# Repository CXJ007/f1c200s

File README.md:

# f1c200s
做这个板子最初目的就是白嫖正点原子的教程，如果买板子按照我以前学习经历大多都是学习下外设那些的然后板子就吃灰了  
这个板子大部分都已经调通了（除了声音因为忘记买芯片后面过年又鸽了）  
还有值得注意的就是usbid 也就是pe2一不注意给占用了，板子上缺少按键学习的时候不太方便  

我是第一次画4层板，还是有很多不足的地方，用来学习应该没问题  
大致流程就是在社区帮助下移植好linux就可以白嫖了注意设备树添加是不一样的  
kicad6.0 ubuntu18 linux5.7.1  
最后附上社区地址https://whycan.com/

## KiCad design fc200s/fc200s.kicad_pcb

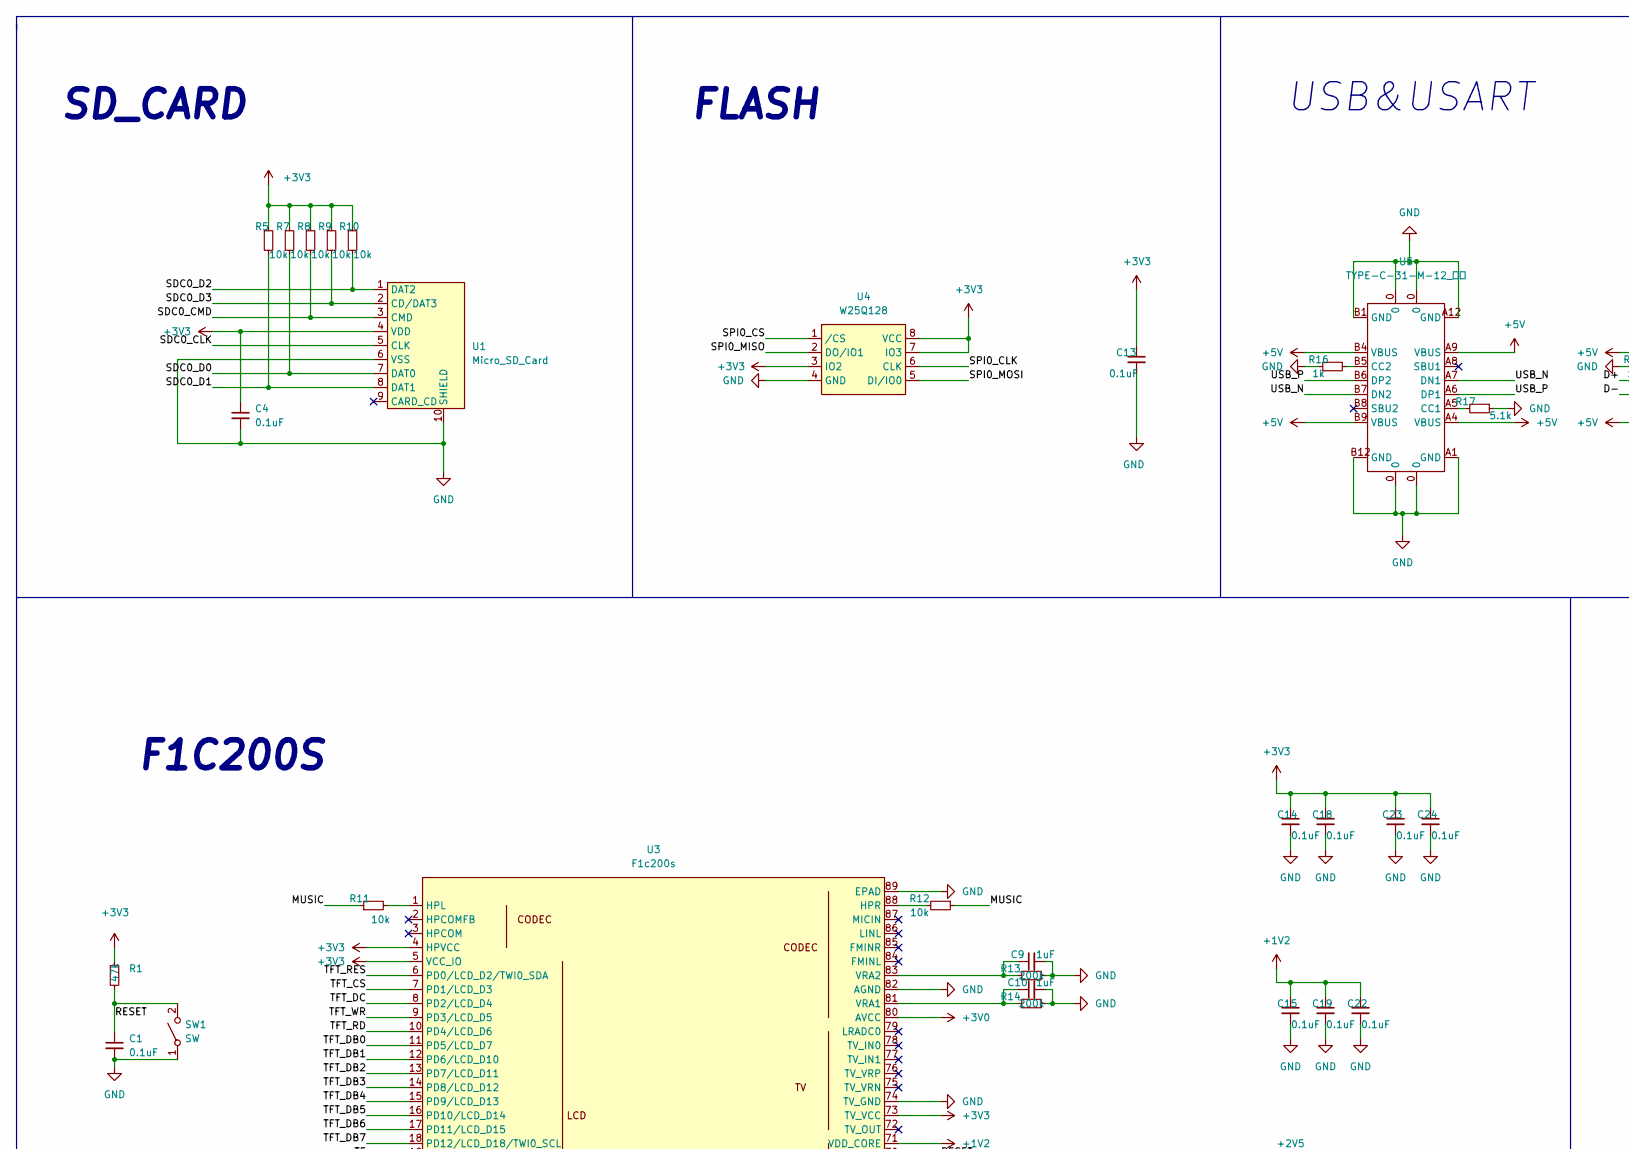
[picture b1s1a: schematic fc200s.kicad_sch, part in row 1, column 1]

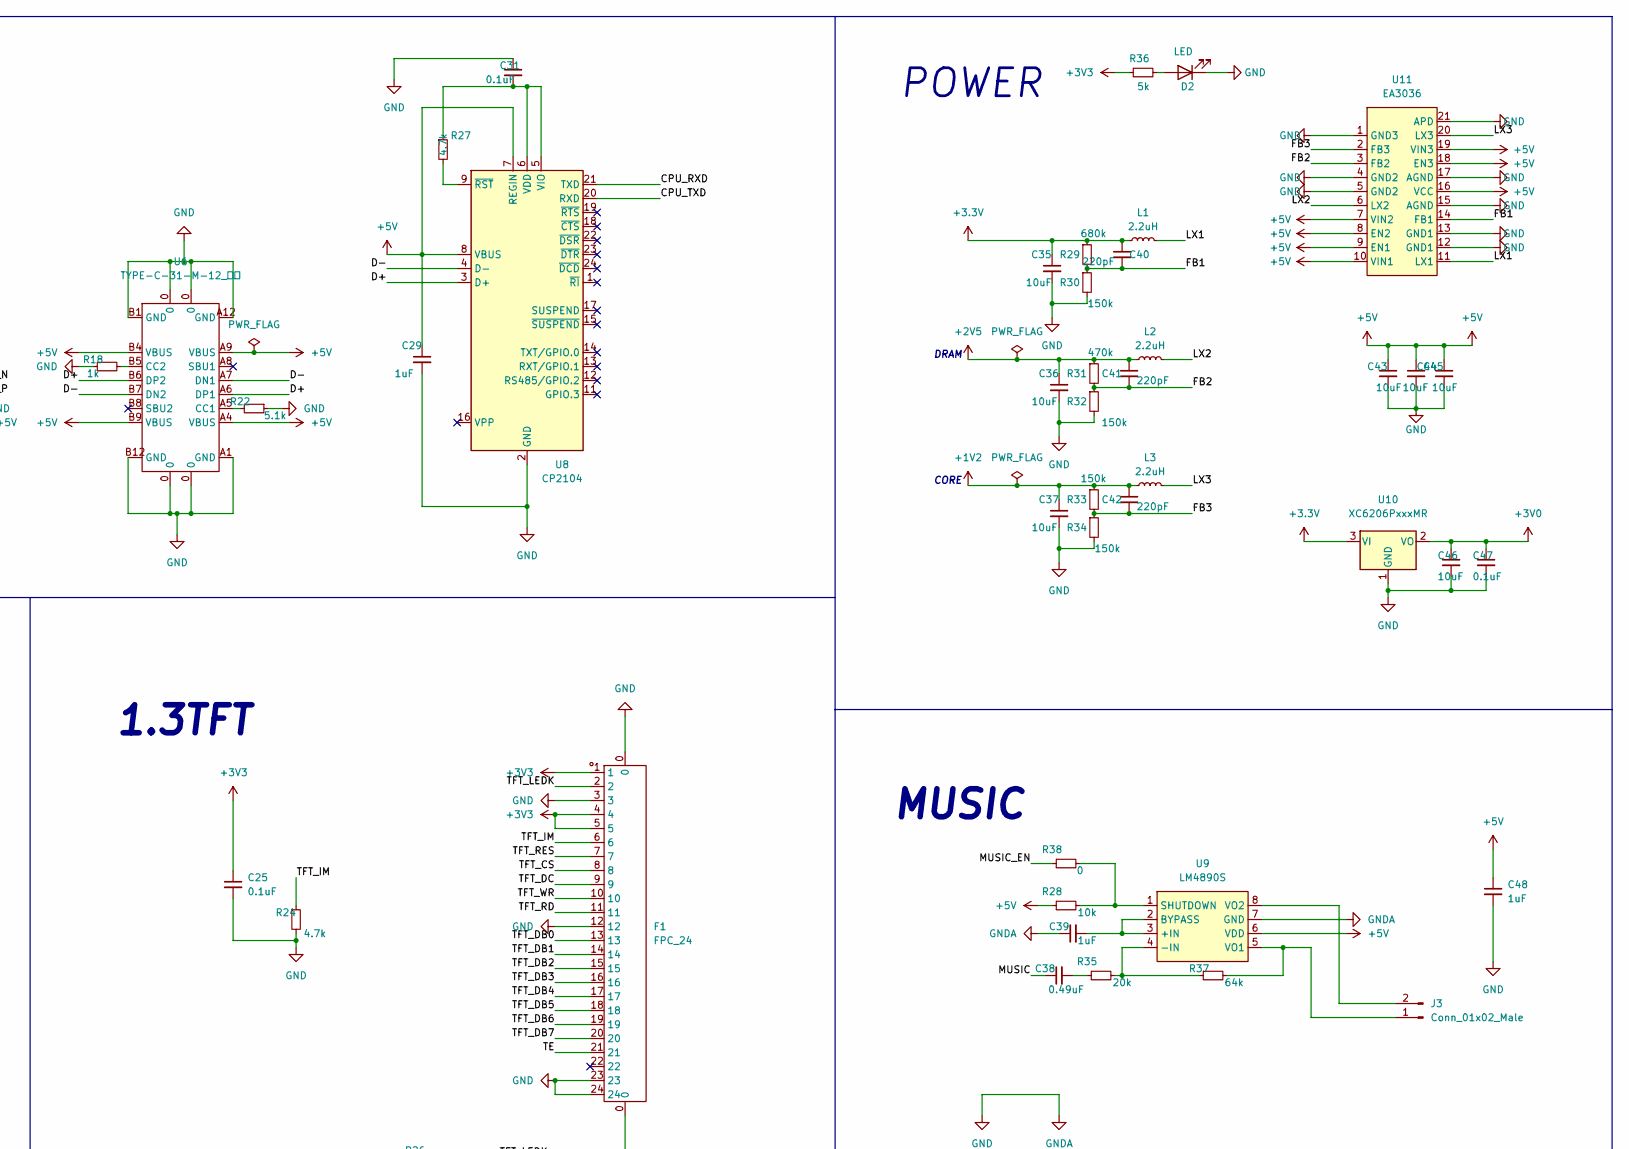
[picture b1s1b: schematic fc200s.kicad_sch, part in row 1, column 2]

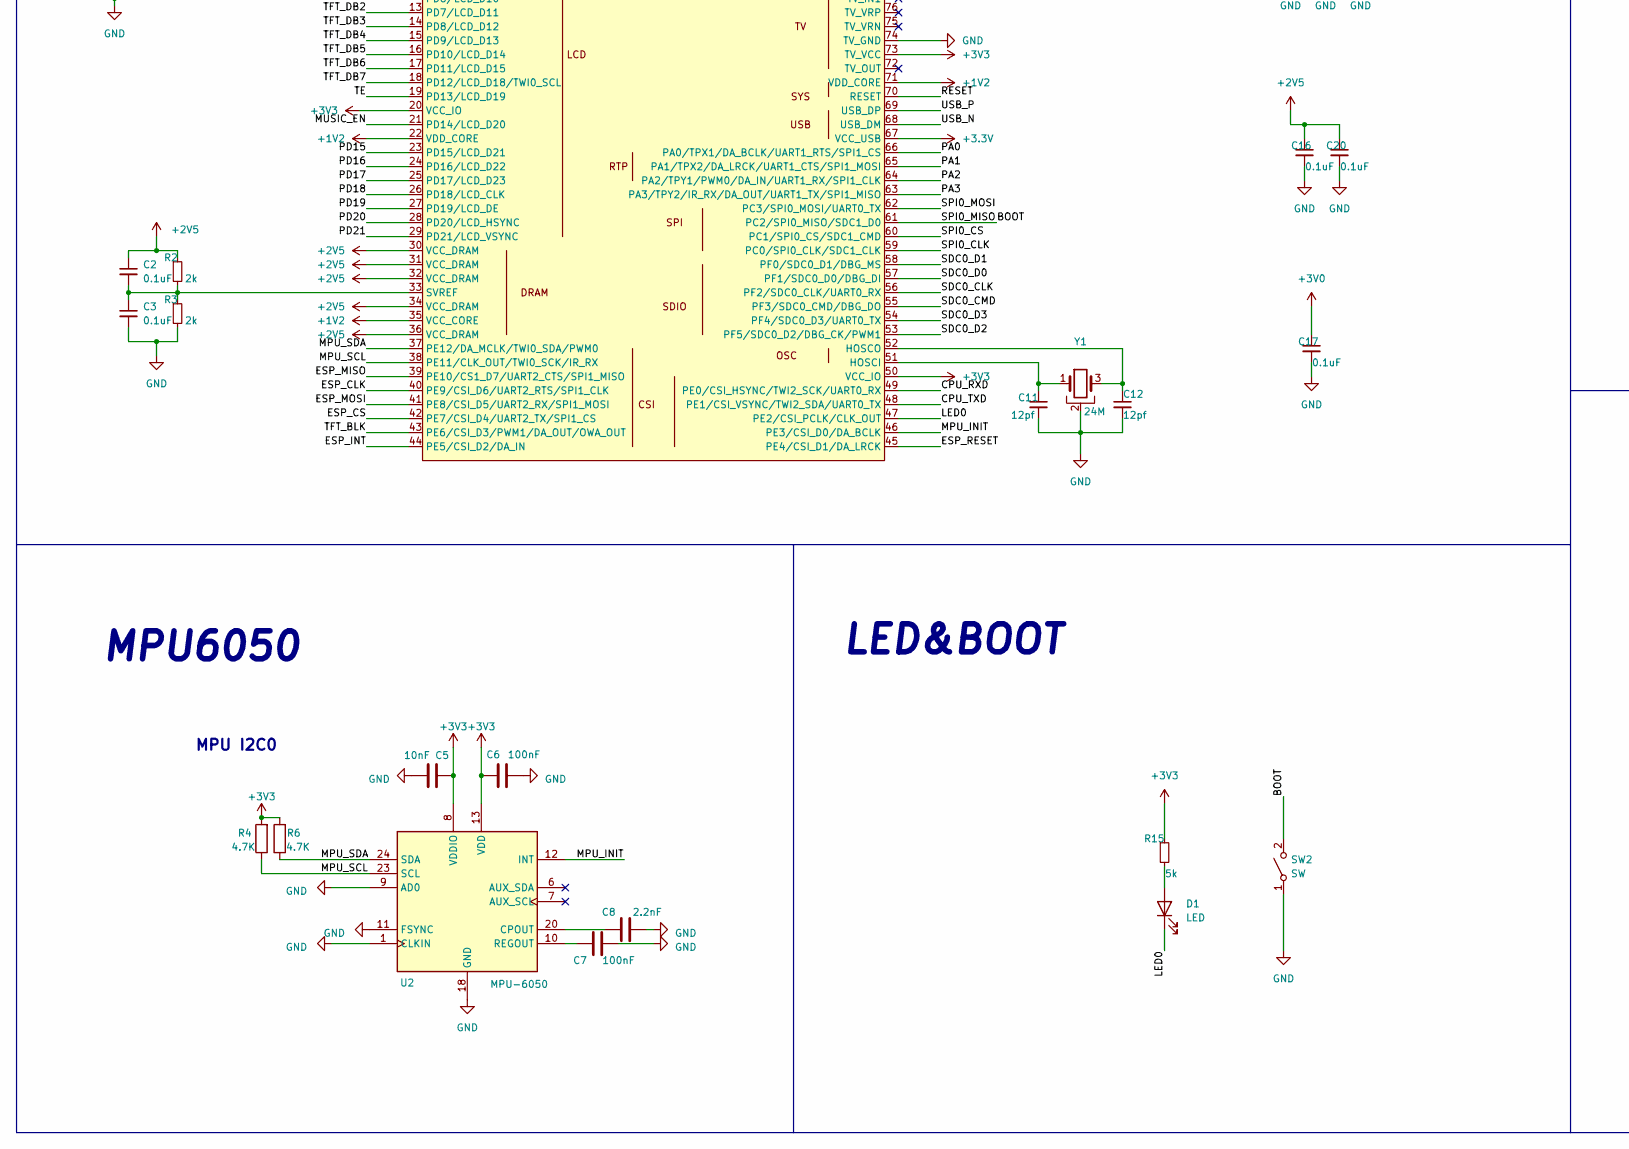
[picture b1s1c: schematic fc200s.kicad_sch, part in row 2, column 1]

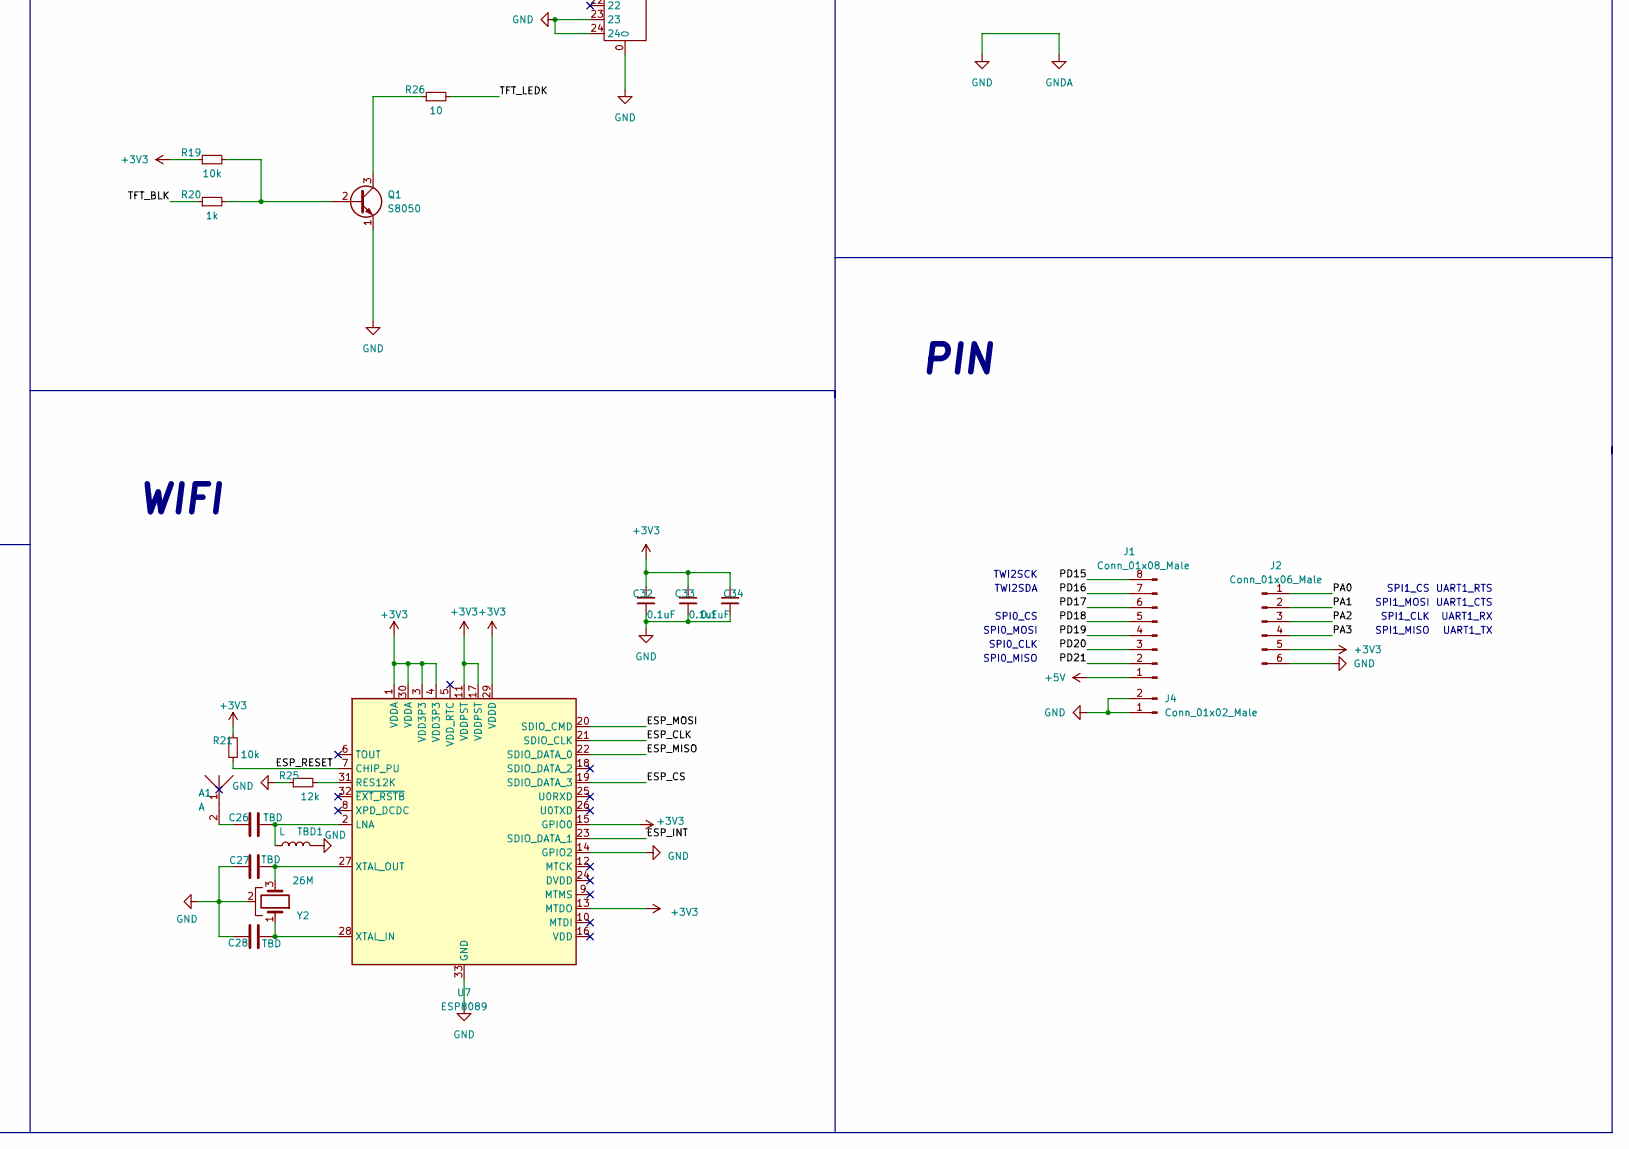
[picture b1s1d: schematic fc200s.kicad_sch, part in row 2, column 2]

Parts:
A1: A; AN9520-245
C1, C2, C3, C4, C13, C14, C15, C16, C17, C18, C19, C20, C22, C23, C24, C25, C31, C32, C33, C34, C47: 0.1uF; C_0805_2012Metric
C5: 10nF; C_0805_2012Metric
C6, C7: 100nF; C_0805_2012Metric
C8: 2.2nF; C_0805_2012Metric
C9, C10, C29, C39, C48: 1uF; C_0805_2012Metric
C11, C12: 12pf; C_0805_2012Metric
C26, C27, C28: TBD; C_0805_2012Metric
C35, C36, C37, C43, C44, C45, C46: 10uF; C_0805_2012Metric
C38: 0.49uF; C_0805_2012Metric
C40, C41, C42: 220pF; C_0805_2012Metric
D1, D2: LED; LED_0805_2012Metric
F1: FPC_24; FPC_24_0.5
J1: Conn_01x08_Male; 8p_2.54
J2: Conn_01x06_Male; 6p_2.54
J3, J4: Conn_01x02_Male; 2p_2.54
L1, L2, L3: 2.2uH; L_0805_2012Metric
Q1: S8050; S8050_SOT_23
R1: 47k; R_0805_2012Metric
R2, R3: 2k; R_0805_2012Metric
R4, R6: 4.7K; R_0805_2012Metric
R5, R7, R8, R9, R10, R11, R12, R19, R21, R28: 10k; R_0805_2012Metric
R13, R14: 200k; R_0805_2012Metric
R15, R36: 5k; R_0805_2012Metric
R16, R18, R20: 1k; R_0805_2012Metric
R17, R22: 5.1k; R_0805_2012Metric
R24, R27: 4.7k; R_0805_2012Metric
R25: 12k; R_0805_2012Metric
R26: 10; R_0805_2012Metric
R29: 680k; R_0805_2012Metric
R30, R32, R33, R34: 150k; R_0805_2012Metric
R31: 470k; R_0805_2012Metric
R35: 20k; R_0805_2012Metric
R37: 64k; R_0805_2012Metric
R38: 0; R_0805_2012Metric
SW1, SW2: SW
TBD1: L; L_0805_2012Metric
U1: Micro_SD_Card; Micro_SD
U2: MPU-6050; InvenSense_QFN-24_4x4mm_P0.5mm
U3: F1c200s; QFN-88_EP_10x10_Pitch0.4mm
U4: W25Q128
U5, U6: TYPE-C-31-M-12_母座; typec 12
U7: ESP8089; QFN-32-1EP_5x5mm_P0.5mm_EP3.1x3.1mm_ThermalVias
U8: CP2104; QFN-24-1EP_4x4mm_P0.5mm_EP2.6x2.6mm
U9: LM4890S; LM4890S_MSOP_8
U10: XC6206PxxxMR; SOT-23
U11: EA3036; QFN-20-1EP_3x3mm_P0.4mm_EP1.65x1.65mm
Y1: 24M; X322512MSB4S
Y2: 26M; X322512MSB4S

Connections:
+1V2: C15.1, C19.1, C22.1, C37.1, C42.1, L3.1, R33.1, U3.22 (VDD_CORE), U3.35 (VCC_CORE), U3.71 (VDD_CORE)
+2V5: C2.1, C16.1, C20.1, C36.1, C41.1, L2.1, R2.1, R31.1, U3.30 (VCC_DRAM), U3.31 (VCC_DRAM), U3.32 (VCC_DRAM), U3.34 (VCC_DRAM), U3.36 (VCC_DRAM)
+3V0: C17.1, C46.1, C47.1, U3.80 (AVCC), U10.2 (VO)
+5V: C29.1, C43.1, C44.1, C45.1, C48.1, J1.1, R28.1, U5.A4 (VBUS), U5.A9 (VBUS), U5.B4 (VBUS), U5.B9 (VBUS), U6.A4 (VBUS), U6.A9 (VBUS), U6.B4 (VBUS), U6.B9 (VBUS), U8.7 (REGIN), U8.8 (VBUS), U9.6 (VDD), U11.7 (VIN2), U11.8 (EN2), U11.9 (EN1), U11.10 (VIN1), U11.16 (VCC), U11.18 (EN3), U11.19 (VIN3)
/BOOT: SW2.2 (B), U3.61 (PC2/SPI0_MISO/SDC1_D0), U4.2 (DO/IO1)
/CPU_RXD: U3.49 (PE0/CSI_HSYNC/TWI2_SCK/UART0_RX), U8.21 (TXD)
/CPU_TXD: U3.48 (PE1/CSI_VSYNC/TWI2_SDA/UART0_TX), U8.20 (RXD)
/D+: U6.A6 (DP1), U6.B6 (DP2), U8.3 (D+)
/D-: U6.A7 (DN1), U6.B7 (DN2), U8.4 (D-)
/ESP_CLK: U3.40 (PE9/CSI_D6/UART2_RTS/SPI1_CLK), U7.21 (SDIO_CLK)
/ESP_CS: U3.42 (PE7/CSI_D4/UART2_TX/SPI1_CS), U7.19 (SDIO_DATA_3)
/ESP_INT: U3.44 (PE5/CSI_D2/DA_IN), U7.23 (SDIO_DATA_1)
/ESP_MISO: U3.39 (PE10/CS1_D7/UART2_CTS/SPI1_MISO), U7.22 (SDIO_DATA_0)
/ESP_MOSI: U3.41 (PE8/CSI_D5/UART2_RX/SPI1_MOSI), U7.20 (SDIO_CMD)
/ESP_RESET: R21.2, U3.45 (PE4/CSI_D1/DA_LRCK), U7.7 (CHIP_PU)
/FB1: C40.2, R29.2, R30.1, U11.14 (FB1)
/FB2: C41.2, R31.2, R32.1, U11.3 (FB2)
/FB3: C42.2, R33.2, R34.1, U11.2 (FB3)
/LED0: D1.1 (K), U3.47 (PE2/CSI_PCLK/CLK_OUT)
/LX1: L1.2, U11.11 (LX1)
/LX2: L2.2, U11.6 (LX2)
/LX3: L3.2, U11.20 (LX3)
/MPU_INIT: U2.12 (INT), U3.46 (PE3/CSI_D0/DA_BCLK)
/MPU_SCL: R4.1, U2.23 (SCL), U3.38 (PE11/CLK_OUT/TWI0_SCK/IR_RX)
/MPU_SDA: R6.1, U2.24 (SDA), U3.37 (PE12/DA_MCLK/TWI0_SDA/PWM0)
/MUSIC: C38.1, R11.1, R12.1
/MUSIC_EN: R38.1, U3.21 (PD14/LCD_D20)
/PA0: J2.1, U3.66 (PA0/TPX1/DA_BCLK/UART1_RTS/SPI1_CS)
/PA1: J2.2, U3.65 (PA1/TPX2/DA_LRCK/UART1_CTS/SPI1_MOSI)
/PA2: J2.3, U3.64 (PA2/TPY1/PWM0/DA_IN/UART1_RX/SPI1_CLK)
/PA3: J2.4, U3.63 (PA3/TPY2/IR_RX/DA_OUT/UART1_TX/SPI1_MISO)
/PD15: J1.8, U3.23 (PD15/LCD_D21)
/PD16: J1.7, U3.24 (PD16/LCD_D22)
/PD17: J1.6, U3.25 (PD17/LCD_D23)
/PD18: J1.5, U3.26 (PD18/LCD_CLK)
/PD19: J1.4, U3.27 (PD19/LCD_DE)
/PD20: J1.3, U3.28 (PD20/LCD_HSYNC)
/PD21: J1.2, U3.29 (PD21/LCD_VSYNC)
/RESET: C1.1, R1.2, SW1.2 (B), U3.70 (RESET)
/SDC0_CLK: U1.5 (CLK), U3.56 (PF2/SDC0_CLK/UART0_RX)
/SDC0_CMD: R8.2, U1.3 (CMD), U3.55 (PF3/SDC0_CMD/DBG_DO)
/SDC0_D0: R7.2, U1.7 (DAT0), U3.57 (PF1/SDC0_D0/DBG_DI)
/SDC0_D1: R5.2, U1.8 (DAT1), U3.58 (PF0/SDC0_D1/DBG_MS)
/SDC0_D2: R10.2, U1.1 (DAT2), U3.53 (PF5/SDC0_D2/DBG_CK/PWM1)
/SDC0_D3: R9.2, U1.2 (CD/DAT3), U3.54 (PF4/SDC0_D3/UART0_TX)
/SPI0_CLK: U3.59 (PC0/SPI0_CLK/SDC1_CLK), U4.6 (CLK)
/SPI0_CS: U3.60 (PC1/SPI0_CS/SDC1_CMD), U4.1 (/CS)
/SPI0_MOSI: U3.62 (PC3/SPI0_MOSI/UART0_TX), U4.5 (DI/IO0)
/TE: F1.21, U3.19 (PD13/LCD_D19)
/TFT_BLK: R20.1, U3.43 (PE6/CSI_D3/PWM1/DA_OUT/OWA_OUT)
/TFT_CS: F1.8, U3.7 (PD1/LCD_D3)
/TFT_DB0: F1.13, U3.11 (PD5/LCD_D7)
/TFT_DB1: F1.14, U3.12 (PD6/LCD_D10)
/TFT_DB2: F1.15, U3.13 (PD7/LCD_D11)
/TFT_DB3: F1.16, U3.14 (PD8/LCD_D12)
/TFT_DB4: F1.17, U3.15 (PD9/LCD_D13)
/TFT_DB5: F1.18, U3.16 (PD10/LCD_D14)
/TFT_DB6: F1.19, U3.17 (PD11/LCD_D15)
/TFT_DB7: F1.20, U3.18 (PD12/LCD_D18/TWI0_SCL)
/TFT_DC: F1.9, U3.8 (PD2/LCD_D4)
/TFT_IM: F1.6, R24.1
/TFT_LEDK: F1.2, R26.2
/TFT_RD: F1.11, U3.10 (PD4/LCD_D6)
/TFT_RES: F1.7, U3.6 (PD0/LCD_D2/TWI0_SDA)
/TFT_WR: F1.10, U3.9 (PD3/LCD_D5)
/USB_N: U3.68 (USB_DM), U5.A7 (DN1), U5.B7 (DN2)
/USB_P: U3.69 (USB_DP), U5.A6 (DP1), U5.B6 (DP2)
GND: C1.2, C3.2, C4.2, C5.2, C6.2, C7.2, C8.2, C9.2, C10.2, C11.2, C12.2, C13.2, C14.2, C15.2, C16.2, C17.2, C18.2, C19.2, C20.2, C22.2, C23.2, C24.2, C25.2, C27.1, C28.1, C29.2, C31.1, C32.2, C33.2, C34.2, C35.2, C36.2, C37.2, C39.1, C43.2, C44.2, C45.2, C46.2, C47.2, C48.2, D2.1 (K), F1.0, F1.3, F1.12, F1.23, F1.24, J2.6, J4.1, J4.2, Q1.1 (E), R3.2, R13.2, R14.2, R16.1, R17.1, R18.1, R22.1, R24.2, R25.1, R30.2, R32.2, R34.2, SW1.1 (A), SW2.1 (A), TBD1.2, U1.6 (VSS), U1.10 (SHIELD), U2.1 (CLKIN), U2.9 (AD0), U2.11 (FSYNC), U2.18 (GND), U3.74 (TV_GND), U3.82 (AGND), U3.89 (EPAD), U4.4 (GND), U5.0, U5.A1 (GND), U5.A12 (GND), U5.B1 (GND), U5.B12 (GND), U6.0, U6.A1 (GND), U6.A12 (GND), U6.B1 (GND), U6.B12 (GND), U7.14 (GPIO2), U7.33 (GND), U8.2 (GND), U8.25 (GND), U9.7 (GND), U10.1 (GND), U11.1 (GND3), U11.4 (GND2), U11.5 (GND2), U11.12 (GND1), U11.13 (GND1), U11.15 (AGND), U11.17 (AGND), U11.21 (APD), Y1.2, Y2.2
unnamed: A1.2, C26.1
unnamed: C2.2, C3.1, R2.2, R3.1, U3.33 (SVREF)
unnamed: C7.1, U2.10 (REGOUT)
unnamed: C8.1, U2.20 (CPOUT)
unnamed: C9.1, R13.1, U3.83 (VRA2)
unnamed: C10.1, R14.1, U3.81 (VRA1)
unnamed: C11.1, U3.51 (HOSCI), Y1.1
unnamed: C12.1, U3.52 (HOSCO), Y1.3
unnamed: C26.2, TBD1.1, U7.2 (LNA)
unnamed: C27.2, U7.27 (XTAL_OUT), Y2.3
unnamed: C28.2, U7.28 (XTAL_IN), Y2.1
unnamed: C31.2, R27.1, U8.5 (VIO), U8.6 (VDD)
unnamed: C38.2, R35.1
unnamed: C39.2, U9.2 (BYPASS), U9.3 (+IN)
unnamed: D1.2 (A), R15.2
unnamed: D2.2 (A), R36.2
unnamed: J3.1, R37.2, U9.5 (VO1)
unnamed: J3.2, U9.8 (VO2)
unnamed: Q1.2 (B), R19.2, R20.2
unnamed: Q1.3 (C), R26.1
unnamed: R11.2, U3.1 (HPL)
unnamed: R12.2, U3.88 (HPR)
unnamed: R16.2, U5.B5 (CC2)
unnamed: R17.2, U5.A5 (CC1)
unnamed: R18.2, U6.B5 (CC2)
unnamed: R22.2, U6.A5 (CC1)
unnamed: R25.2, U7.31 (RES12K)
unnamed: R27.2, U8.9 (~RST)
unnamed: R28.2, R38.2, U9.1 (SHUTDOWN)
unnamed: R35.2, R37.1, U9.4 (-IN)

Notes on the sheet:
LED&BOOT
POWER
PIN
USB&USART
UART1_TX
MPU I2C0
MUSIC
FLASH
WIFI
UART1_CTS
SPI1_MISO
CORE
SPI0_CLK
DRAM
TWI2SDA
F1C200S
UART1_RTS
SPI1_CS
SPI1_MOSI
SPI1_CLK
SPI0_CS
SPI0_MISO
MPU6050
SD_CARD
SPI0_MOSI
UART1_RX
TWI2SCK
1.3TFT

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
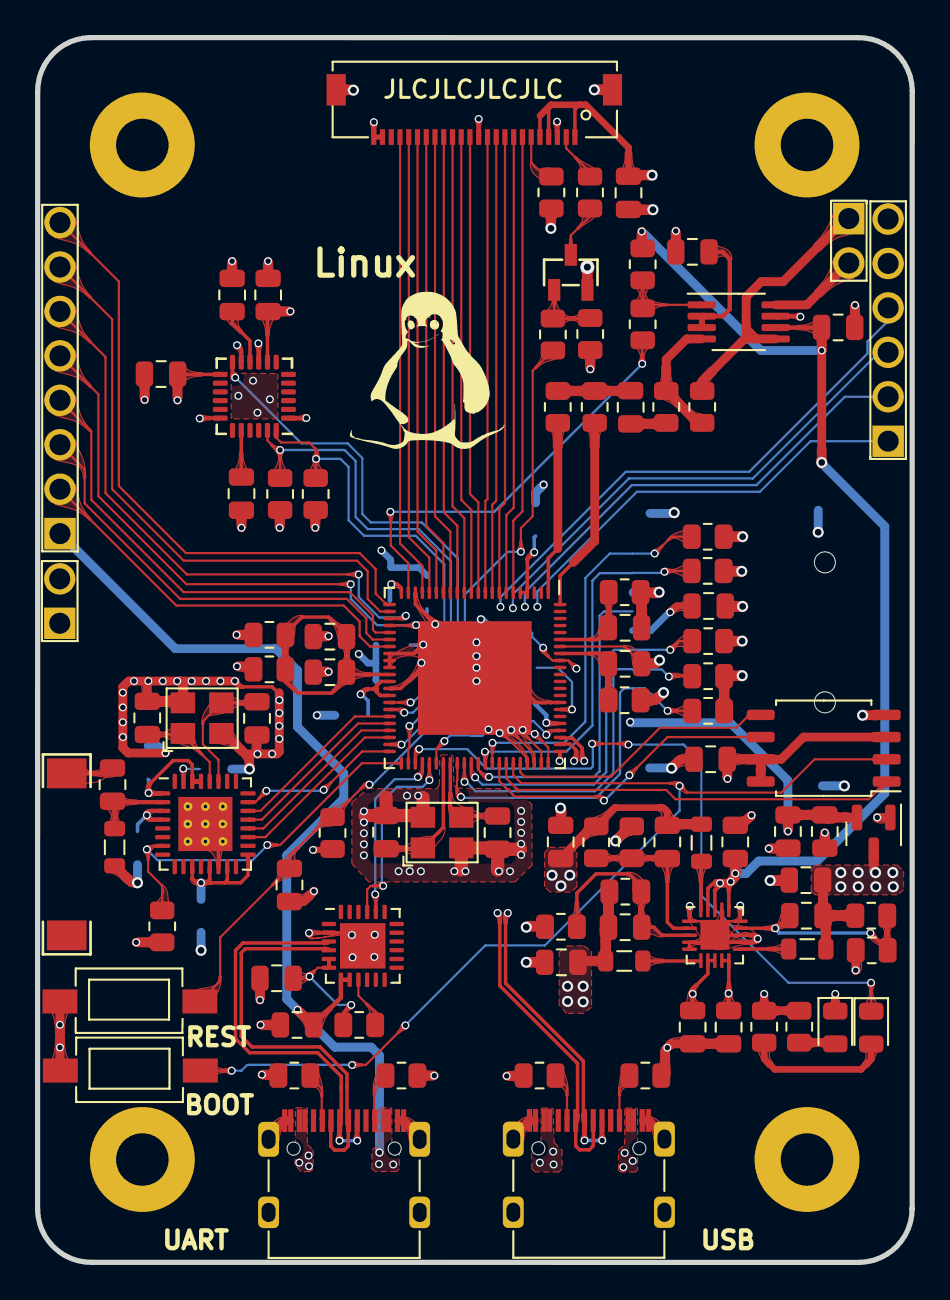
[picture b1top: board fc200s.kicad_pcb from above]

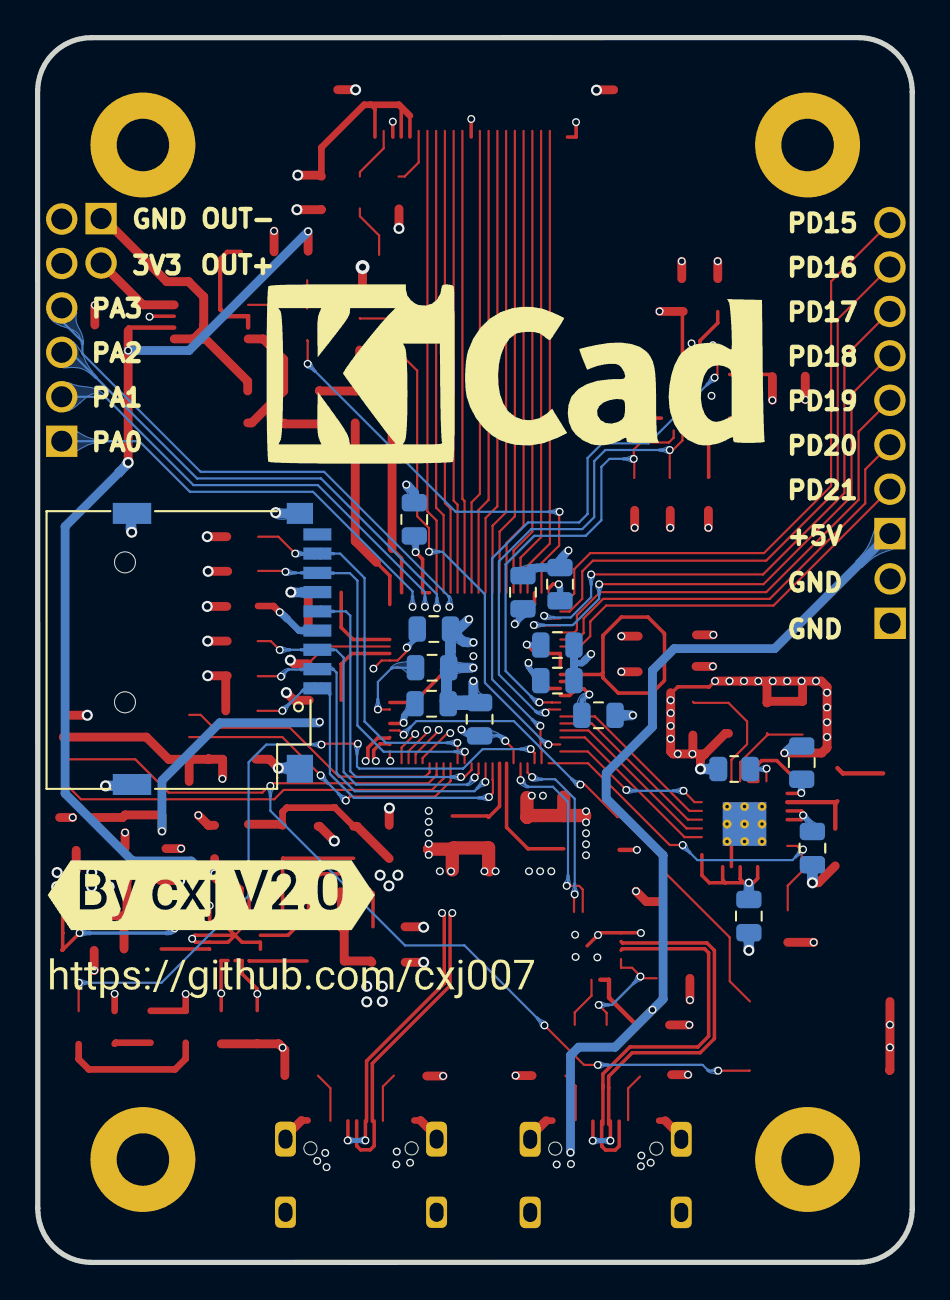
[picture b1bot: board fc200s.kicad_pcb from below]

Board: 4 copper layers, 50.0 x 70.0 mm, 113 parts (17 on the bottom side), 99 nets.

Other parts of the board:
kibuzzard-616427ED: G***; kibuzzard-616427ED
kibuzzard-61642942: G***; kibuzzard-61642942

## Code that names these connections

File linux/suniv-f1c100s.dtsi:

// SPDX-License-Identifier: (GPL-2.0+ OR X11)
/*
 * Copyright 2018 Icenowy Zheng <icenowy@aosc.io>
 * Copyright 2018 Mesih Kilinc <mesihkilinc@gmail.com>
 */

#include <dt-bindings/clock/suniv-ccu-f1c100s.h>
#include <dt-bindings/reset/suniv-ccu-f1c100s.h>
#include <dt-bindings/interrupt-controller/irq.h>
#include <dt-bindings/gpio/gpio.h>
#include <dt-bindings/leds/common.h>

/ {
	#address-cells = <1>;
	#size-cells = <1>;
	interrupt-parent = <&intc>;

	clocks {
		osc24M: clk-24M {
			#clock-cells = <0>;
			compatible = "fixed-clock";
			clock-frequency = <24000000>;
			clock-output-names = "osc24M";
		};

		osc32k: clk-32k {
			#clock-cells = <0>;
			compatible = "fixed-clock";
			clock-frequency = <32768>;
			clock-output-names = "osc32k";
		};
	};

	cpus {
		cpu {
			compatible = "arm,arm926ej-s";
			device_type = "cpu";
		};
	};

	soc {
		compatible = "simple-bus";
		#address-cells = <1>;
		#size-cells = <1>;
		ranges;

		sram-controller@1c00000 {
			compatible = "allwinner,suniv-f1c100s-system-control",
				     "allwinner,sun4i-a10-system-control";
			reg = <0x01c00000 0x30>;
			#address-cells = <1>;
			#size-cells = <1>;
			ranges;

			sram_d: sram@10000 {
				compatible = "mmio-sram";
				reg = <0x00010000 0x1000>;
				#address-cells = <1>;
				#size-cells = <1>;
				ranges = <0 0x00010000 0x1000>;

				otg_sram: sram-section@0 {
					compatible = "allwinner,suniv-f1c100s-sram-d",
						     "allwinner,sun4i-a10-sram-d";
					reg = <0x0000 0x1000>;
					status = "disabled";
				};
			};
		};

		ccu: clock@1c20000 {
			compatible = "allwinner,suniv-f1c100s-ccu";
			reg = <0x01c20000 0x400>;
			clocks = <&osc24M>, <&osc32k>;
			clock-names = "hosc", "losc";
			#clock-cells = <1>;
			#reset-cells = <1>;
		};

		intc: interrupt-controller@1c20400 {
			compatible = "allwinner,suniv-f1c100s-ic";
			reg = <0x01c20400 0x400>;
			interrupt-controller;
			#interrupt-cells = <1>;
		};

		pio: pinctrl@1c20800 {
			compatible = "allwinner,suniv-f1c100s-pinctrl";
			reg = <0x01c20800 0x400>;
			interrupts = <38>, <39>, <40>;
			clocks = <&ccu 37>, <&osc24M>, <&osc32k>;
			clock-names = "apb", "hosc", "losc";
			gpio-controller;
			interrupt-controller;
			#interrupt-cells = <3>;
			#gpio-cells = <3>;

			uart0_pe_pins: uart0-pe-pins {
				pins = "PE0", "PE1";
				function = "uart0";
			};

			mmc0_pins: mmc0-pins {
                pins = "PF0", "PF1", "PF2", "PF3", "PF4", "PF5";
                function = "mmc0";
            };

			i2c0_pe_pins: i2c0-pe-pins {
				pins = "PE11", "PE12";
				function = "i2c0";
			};

			spi0_pd_pins: spi0-pd-pins {
                pins = "PD20","PD18","PD21","PD19";
                function = "spi0";
            };

			spi1_pe_pins: spi1-pe-pins {
                pins = "PE9","PE7","PE10","PE8";
                function = "spi1";
            };

			led_pins: led-pins {
                pins = "PE2";
                function = "led";
            };

			key_pins: key-pins {
                pins = "PD15";
                function = "key";
            };

			// irq_pins: irq_pins {
            //     pins = "PD16";
            //     function = "irq";
            // };

			tft_pins: tft-pins {
                pins = "PD15","PD16","PD17";
                function = "tft";
            };

			tft8_pins: tft8-pins {
				pins = "PD0","PD1","PD2","PD3","PD4","PD5","PD6","PD7",
					"PD8","PD9","PD10","PD11","PD12","PD13";
				function = "ftf8080";
			};

		};

		timer@1c20c00 {
			compatible = "allwinner,suniv-f1c100s-timer";
			reg = <0x01c20c00 0x90>;
			interrupts = <13>;
			clocks = <&osc24M>;
		};

		mmc0: mmc@1c0f000 {
			compatible = "allwinner,suniv-f1c100s-mmc",
				     "allwinner,sun7i-a20-mmc";
			reg = <0x01c0f000 0x1000>;
			clocks = <&ccu CLK_BUS_MMC0>,
				 <&ccu CLK_MMC0>,
				 <&ccu CLK_MMC0_OUTPUT>,
				 <&ccu CLK_MMC0_SAMPLE>;
			clock-names = "ahb",
				      "mmc",
				      "output",
				      "sample";
			resets = <&ccu RST_BUS_MMC0>;
			reset-names = "ahb";
			interrupts = <23>;
			pinctrl-names = "default";
			pinctrl-0 = <&mmc0_pins>;
			status = "disabled";
			#address-cells = <1>;
			#size-cells = <0>;
		};

		wdt: watchdog@1c20ca0 {
			compatible = "allwinner,suniv-f1c100s-wdt",
				     "allwinner,sun4i-a10-wdt";
			reg = <0x01c20ca0 0x20>;
		};

		uart0: serial@1c25000 {
			compatible = "snps,dw-apb-uart";
			reg = <0x01c25000 0x400>;
			interrupts = <1>;
			reg-shift = <2>;
			reg-io-width = <4>;
			clocks = <&ccu 38>;
			resets = <&ccu 24>;
			status = "disabled";
		};

		uart1: serial@1c25400 {
			compatible = "snps,dw-apb-uart";
			reg = <0x01c25400 0x400>;
			interrupts = <2>;
			reg-shift = <2>;
			reg-io-width = <4>;
			clocks = <&ccu 39>;
			resets = <&ccu 25>;
			status = "disabled";
		};

		uart2: serial@1c25800 {
			compatible = "snps,dw-apb-uart";
			reg = <0x01c25800 0x400>;
			interrupts = <3>;
			reg-shift = <2>;
			reg-io-width = <4>;
			clocks = <&ccu 40>;
			resets = <&ccu 26>;
			status = "disabled";
		};

		i2c0: i2c@1c27000 {
			compatible = "allwinner,sun6i-a31-i2c";
			reg = <0x01c27000 0x400>;
			interrupts = <7>;
			clocks = <&ccu CLK_BUS_I2C0>;
			resets = <&ccu RST_BUS_I2C0>;
			pinctrl-names = "default";
			pinctrl-0 = <&i2c0_pe_pins>;
			status = "disabled";
			#address-cells = <1>;
			#size-cells = <0>;
		};

		spi0: spi@1c05000 {
            compatible = "allwinner,suniv-spi",
                     "allwinner,sun8i-h3-spi";
            reg = <0x01c05000 0x1000>;
            interrupts = <10>;
            clocks = <&ccu CLK_BUS_SPI0>, <&ccu CLK_BUS_SPI0>;
            clock-names = "ahb", "mod";
            resets = <&ccu RST_BUS_SPI0>;
            status = "disabled";
            #address-cells = <1>;
            #size-cells = <0>;
        };

		spi1: spi@1c06000 {
			compatible = "allwinner,suniv-f1c100s-spi",
					 "allwinner,sun8i-h3-spi";
			reg = <0x01c06000 0x1000>;
			interrupts = <11>;
			clocks = <&ccu CLK_BUS_SPI1>, <&ccu CLK_BUS_SPI1>;
			clock-names = "ahb", "mod";
			resets = <&ccu RST_BUS_SPI1>;
			status = "disabled";
			#address-cells = <1>;
			#size-cells = <0>;
		};
	};
};

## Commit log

2022-02-02 2022/2/2
